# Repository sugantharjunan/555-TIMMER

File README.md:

# 555 Timer Circuit – KiCad PCB Design

A compact and beginner-friendly **555 Timer Circuit** designed using **KiCad EDA** for schematic capture and PCB layout. This project uses the popular **NE555 Timer IC** configured in astable mode to generate continuous pulses for LED blinking applications.

The circuit is ideal for learning timer circuits, PCB designing, pulse generation, and basic embedded electronics.

---

# Project Overview

This project demonstrates:

* NE555 timer astable circuit design
* LED blinking application
* PCB layout using KiCad
* Through-hole component placement
* Pulse generation circuit
* Compact PCB design
* 3D PCB visualization

---

# Features

* LED blinking output
* Astable timer configuration
* Compact PCB layout
* Easy-to-build design
* Through-hole components
* Beginner-friendly electronics project
* Designed using KiCad

---

# Software Used

* KiCad

Official Website: [KiCad Official Website](https://www.kicad.org?utm_source=chatgpt.com)

---

# Hardware Components

| Component      | Description                 |
| -------------- | --------------------------- |
| NE555          | Timer IC                    |
| LED            | Output indicator            |
| Resistors      | Timing and current limiting |
| Capacitor      | Timing capacitor            |
| Screw Terminal | Power input                 |
| DIP Socket     | IC mounting                 |

---

# Project Structure

```bash id="1q6h8r"
555-TIMER/
│
├── Schematic/
│   └── 555_timer.kicad_sch
│
├── PCB/
│   └── 555_timer.kicad_pcb
│
├── Gerber/
│   └── Manufacturing_Files
│
├── Images/
│   ├── 555_TIMER_3D_FRONT.png
│   ├── 555_3D_BACK.png
│   ├── 555_PCB.png
│   └── 555_SCHEMATIC.png
│
└── README.md
```

---

# Circuit Description

The circuit uses the **NE555 Timer IC** configured in **astable mode**.

In this mode:

* The output continuously switches between HIGH and LOW states.
* The LED connected to the output pin blinks repeatedly.
* The timing depends on resistor and capacitor values.

---

# Working Principle

1. Power supply is connected through the screw terminal.
2. The NE555 generates periodic pulses.
3. Timing capacitor charges and discharges continuously.
4. Output pin toggles between HIGH and LOW states.
5. LED blinks according to generated timing pulses.

---

# PCB Design

The PCB was designed with:

* Compact board dimensions
* Clean routing structure
* Through-hole component placement
* Easy soldering access
* Organized power and signal traces

---

# Electrical Specifications

| Parameter         | Value             |
| ----------------- | ----------------- |
| Operating Voltage | 5V – 12V DC       |
| Timer IC          | NE555             |
| Configuration     | Astable Mode      |
| Output Type       | Pulse / LED Blink |
| PCB Tool          | KiCad             |

---

# Applications

* LED Flasher Circuits
* Pulse Generation
* Timer Applications
* Electronics Learning
* Embedded Hardware Practice
* Oscillator Circuits

---

# Timing Formula

The output frequency of the NE555 in astable mode is determined by:

f = \frac{1.44}{(R_1 + 2R_2)C}

Where:

* (R_1) and (R_2) are timing resistors
* (C) is the timing capacitor

---

# Future Improvements

* Add potentiometer for adjustable frequency
* Add buzzer output
* Add PWM control
* Add relay driving capability
* Convert to SMD compact version

---

This project is open-source and available under the MIT License.

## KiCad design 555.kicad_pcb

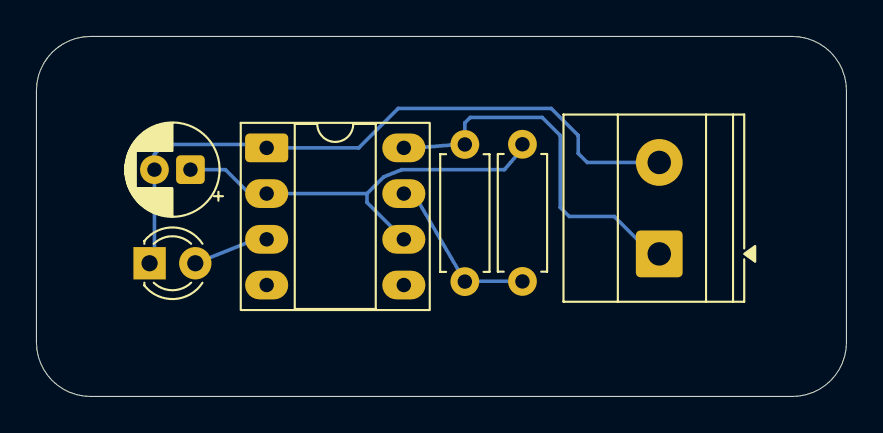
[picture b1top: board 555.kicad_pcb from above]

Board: 2 copper layers, 45.0 x 20.0 mm, 6 parts (0 on the bottom side), 5 nets.

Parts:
C1: 10uf; CP_Radial_D5.0mm_P2.00mm
D1: LED; LED_D3.0mm
J1: Screw_Terminal_01x02; TerminalBlock_Phoenix_MKDS-1,5-2-5.08_1x02_P5.08mm_Horizont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
R1: 10k; R_Axial_DIN0207_L6.3mm_D2.5mm_P7.62mm_Horizontal
R2: 150k; R_Axial_DIN0207_L6.3mm_D2.5mm_P7.62mm_Horizontal
U1: ICM7555xB; DIP-8_W7.62mm_Socket_LongPads

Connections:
+12V: J1.1, R1.1, U1.8 (VCC)
GND: C1.2, D1.1 (K), J1.2, U1.1 (GND)
unnamed: D1.2 (A), U1.3 (Q)
unnamed: R1.2, R2.1, U1.7 (DIS)
unnamed: C1.1, R2.2, U1.2 (TR), U1.6 (THR)
